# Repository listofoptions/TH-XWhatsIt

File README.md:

# TH-XWhatsIt

through hole implementation of the capsense controllers by XWhatsIt
(Tom Wong-Cornell). original liscencure holds, as well as CERN OSH
(compatible license).

original implementation of Tom Wong-Cornell's controller documented here

http://downloads.cornall.co/ibm-capsense-usb-web/ibm-capsense-usb.html

component documentation is supplied, working theory of operation is under
the previous link.

Please read the following files:

* [BOM.md](BOM.md) for Bill Of Materials.
* [ERRATA.md](ERRATA.md) for changes that must be made to older revision boards.
* [CHANGES.txt](CHANGES.txt) for all the detailed changes to this project over time.
* [PCB_ORDERING_INSTRUCTIONS.md](PCB_ORDERING_INSTRUCTIONS.md) for some notes on how to order PCBs.

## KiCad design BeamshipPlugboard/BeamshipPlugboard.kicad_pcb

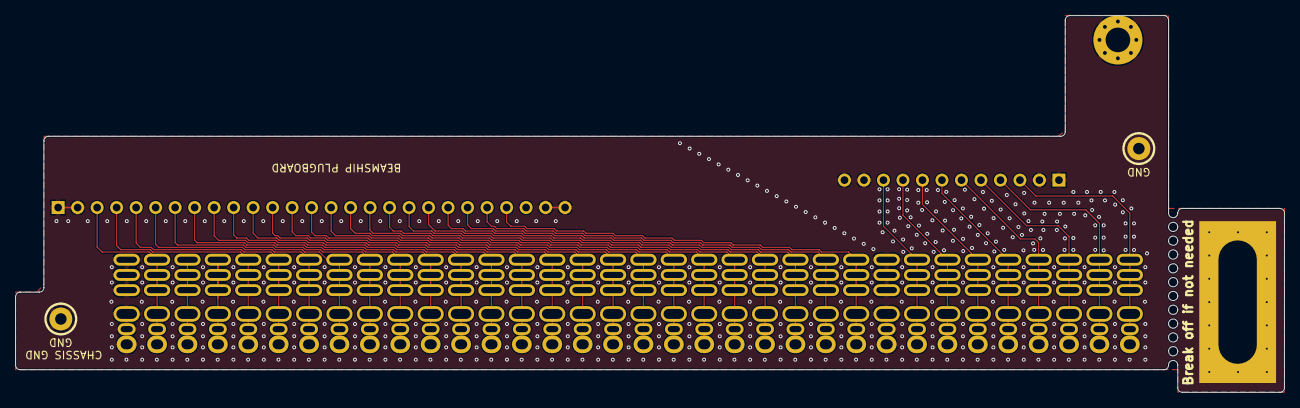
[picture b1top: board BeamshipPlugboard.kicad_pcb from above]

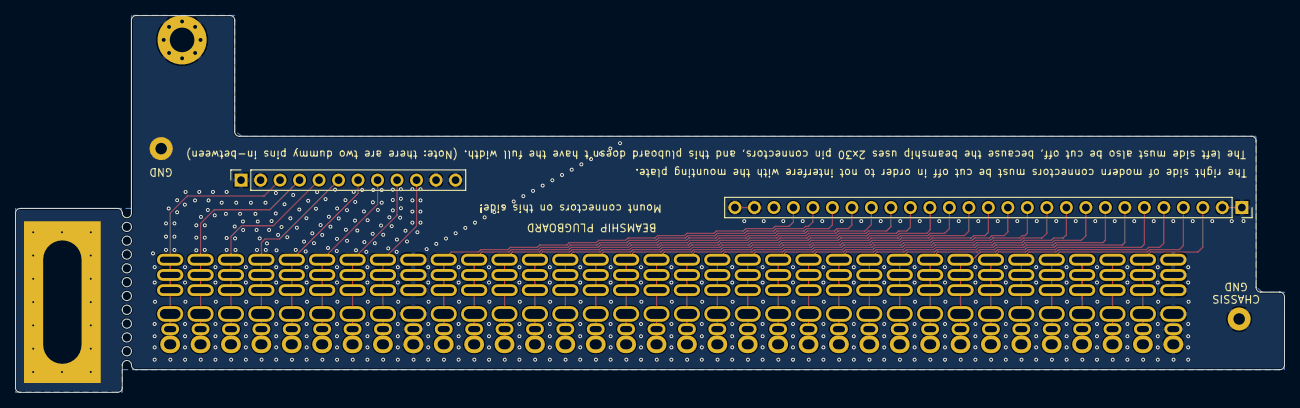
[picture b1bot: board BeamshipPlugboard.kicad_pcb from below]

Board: 2 copper layers, 165.3 x 49.1 mm, 7 parts (2 on the bottom side), 31 nets.

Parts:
H1: Grounded hole for M3 standoff; MountingHole_3.2mm_M3_Pad_Via
H2: BEAMSHIP MOUNTING HOLE; beamship_mounting_hole
H3, H4: GROUND STRAP; ChassisGnd
J1: BEAMSPRING PLUGBOARD COLUMNS; PinSocket_1x27_P2.54mm_Vertical
J2: BEAMSPRING PLUGBOARD ROWS; PinSocket_1x12_P2.54mm_Vertical
J7: Conn_01x34; beamship_new_2

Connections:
/BSCOL1: J1.3, J7.2
/BSCOL2: J1.4, J7.5
/BSCOL3: J1.5, J7.6
/BSCOL4: J1.6, J7.7
/BSCOL5: J1.7, J7.8
/BSCOL6: J1.8, J7.9
/BSCOL7: J1.9, J7.10
/BSCOL8: J1.10, J7.11
/BSCOL9: J1.11, J7.12
/BSCOL10: J1.12, J7.13
/BSCOL11: J1.13, J7.14
/BSCOL12: J1.14, J7.15
/BSCOL13: J1.15, J7.16
/BSCOL14: J1.16, J7.17
/BSCOL15: J1.17, J7.18
/BSCOL16: J1.18, J7.19
/BSCOL17: J1.19, J7.20
/BSCOL18: J1.20, J7.21
/BSCOL19: J1.21, J7.22
/BSCOL20: J1.22, J7.23
/BSCOL21: J1.23, J7.24
/BSCOL22: J1.24, J7.25
/BSGROUND: H1.1, H2.1, H3.1, H4.1, J1.1, J1.2, J1.26, J1.27, J2.1, J2.2, J2.11, J2.12, J7.1, J7.26
/BSSENSE1: J2.10, J7.27
/BSSENSE2: J2.9, J7.28
/BSSENSE3: J2.8, J7.29
/BSSENSE4: J2.7, J7.30
/BSSENSE5: J2.6, J7.31
/BSSENSE6: J2.5, J7.32
/BSSENSE7: J2.4, J7.33
/BSSENSE8: J2.3, J7.34

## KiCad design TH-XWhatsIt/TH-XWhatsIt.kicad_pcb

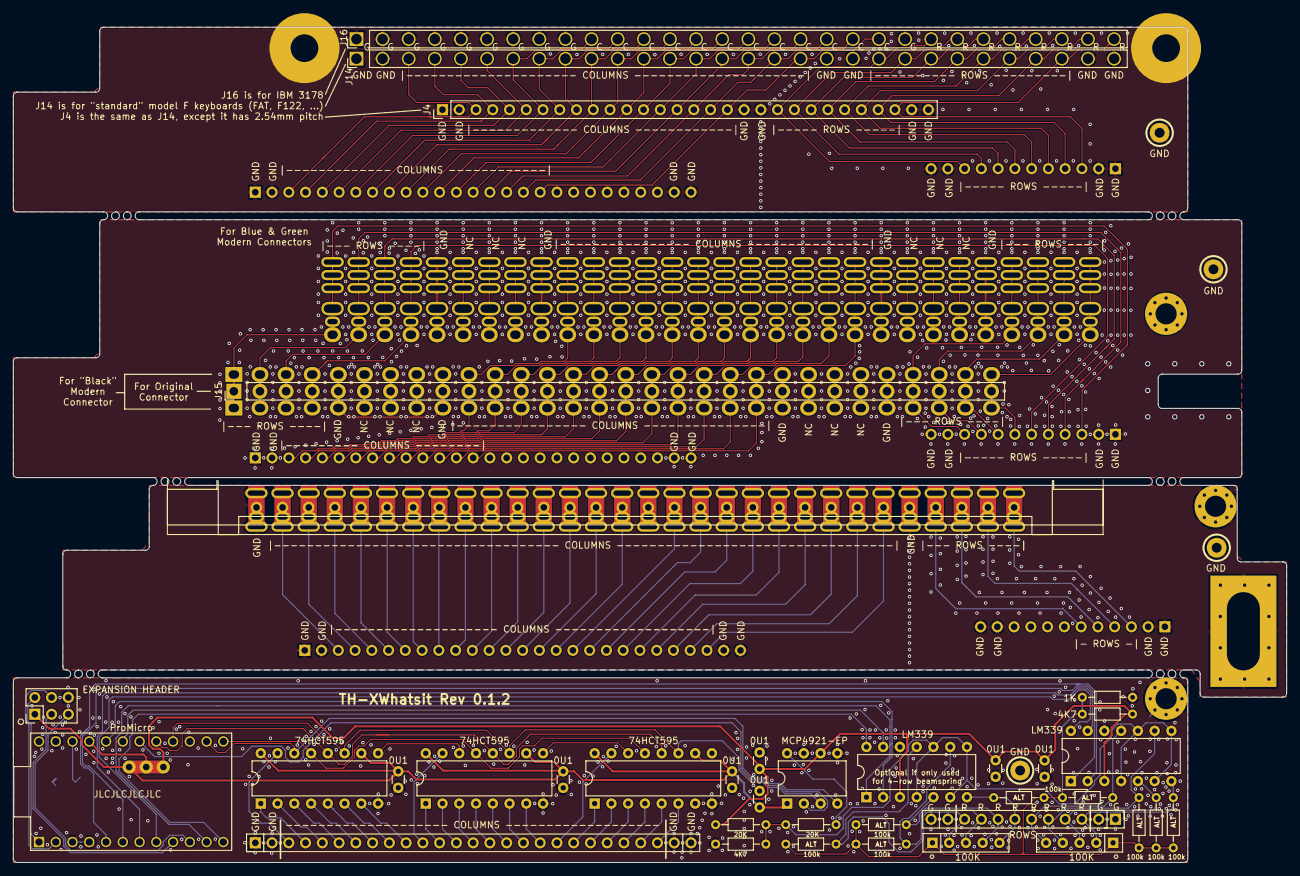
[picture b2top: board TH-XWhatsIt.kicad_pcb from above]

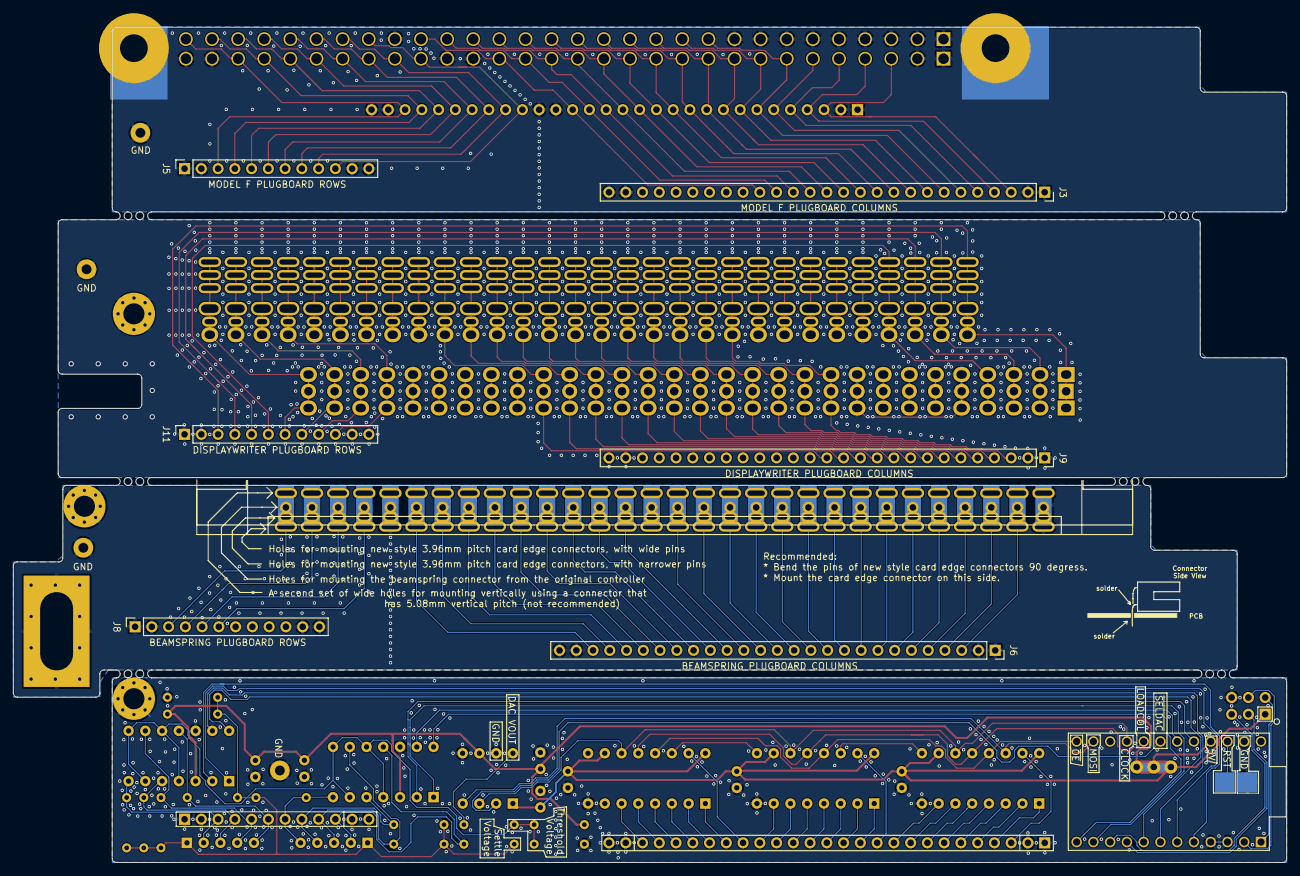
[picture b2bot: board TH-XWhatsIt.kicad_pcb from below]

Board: 2 copper layers, 193.0 x 126.6 mm, 56 parts (9 on the bottom side), 132 nets.

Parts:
C3, C4, C5, C7, C8, C9, C10: 0U1; C_Disc_D3.0mm_W1.6mm_P2.50mm
H1, H3, H4: Grounded hole for M3 standoff; MountingHole_3.2mm_M3_Pad_Via
H5: Beamspring Mounting Hole; BeamSpringGroundingMountingHoleForTHOnly
H6, H7, H8, H9: Solderable ground strap; ChassisGnd
H10: Left Mountinghole; ModelF_new_mounting_hole_left
H11: Right Mountinghole; ModelF_new_mounting_hole_right
J1: COLUMNS; PinHeader_1x27_P2.54mm_Vertical
J2: ROWS; PinHeader_1x12_P2.54mm_Vertical
J3: MODEL F PLUGBOARD COLUMNS; PinSocket_1x27_P2.54mm_Vertical
J4: MODEL F PLUGBOARD CONNECTOR; PinHeader_1x30_P2.54mm_Vertical
J5: MODEL F PLUGBOARD ROWS; PinSocket_1x12_P2.54mm_Vertical
J6: BEAMSPRING PLUGBOARD COLUMNS; PinSocket_1x27_P2.54mm_Vertical
J7: BEAMSPRING PLUGBOARD CONNECTOR; beamspring_connector_footprint
J8: BEAMSPRING PLUGBOARD ROWS; PinSocket_1x12_P2.54mm_Vertical
J9: DISPLAYWRITER PLUGBOARD COLUMNS; PinSocket_1x27_P2.54mm_Vertical
J10: Conn_01x30; displaywriter-connector_v3
J11: DISPLAYWRITER PLUGBOARD ROWS; PinSocket_1x12_P2.54mm_Vertical
J12: EXPANSION HEADER; PinHeader_2x03_P2.54mm_Vertical
J13: Conn_01x02; PadsToShort
J14, J16: MODEL F PLUGBOARD CONNECTOR; Model_F_3.96mm_pitch_footprint
J15: Conn_01x30; Displaywriter_with_mountinghole_footprint
NT2: Net-Tie_3; NetTie-3_THT_Pad1.0mm_mod_thicker
R1, R5: 4K7; R_Axial_DIN0204_L3.6mm_D1.6mm_P7.62mm_Horizontal
R2: 1K; R_Axial_DIN0204_L3.6mm_D1.6mm_P7.62mm_Horizontal
R3, R4: 20K; R_Axial_DIN0204_L3.6mm_D1.6mm_P7.62mm_Horizontal
R6, R7, R8, R9, R10, R11, R12, R13: 100k; R_Axial_DIN0204_L3.6mm_D1.6mm_P7.62mm_Horizontal
RN1, RN3: 100K; R_Array_SIP5
U1, U6: LM339; DIP-14_W7.62mm
U2: MCP4921-EP; DIP-8_W7.62mm
U3, U5, U8: 74HCT595; DIP-16_W7.62mm
U7: ProMicro

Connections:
+5VA: C4.2, C9.2, C10.2, NT2.3, R1.1, R3.2, U1.3, U2.6, U6.3
+5VD: C3.2, C5.2, C7.2, C8.2, J12.1, NT2.1, U2.1, U3.10, U3.16, U5.10, U5.16, U8.10, U8.16
/beamspring plugboard/BSCOL1: J6.3, J7.2
/beamspring plugboard/BSCOL2: J6.4, J7.3
/beamspring plugboard/BSCOL3: J6.5, J7.4
/beamspring plugboard/BSCOL4: J6.6, J7.5
/beamspring plugboard/BSCOL5: J6.7, J7.6
/beamspring plugboard/BSCOL6: J6.8, J7.7
/beamspring plugboard/BSCOL7: J6.9, J7.8
/beamspring plugboard/BSCOL8: J6.10, J7.9
/beamspring plugboard/BSCOL9: J6.11, J7.10
/beamspring plugboard/BSCOL10: J6.12, J7.11
/beamspring plugboard/BSCOL11: J6.13, J7.12
/beamspring plugboard/BSCOL12: J6.14, J7.13
/beamspring plugboard/BSCOL13: J6.15, J7.14
/beamspring plugboard/BSCOL14: J6.16, J7.15
/beamspring plugboard/BSCOL15: J6.17, J7.17
/beamspring plugboard/BSCOL16: J6.18, J7.18
/beamspring plugboard/BSCOL17: J6.19, J7.19
/beamspring plugboard/BSCOL18: J6.20, J7.20
/beamspring plugboard/BSCOL19: J6.21, J7.21
/beamspring plugboard/BSCOL20: J6.22, J7.22
/beamspring plugboard/BSCOL21: J6.23, J7.23
/beamspring plugboard/BSCOL22: J6.24, J7.24
/beamspring plugboard/BSCOL23: J6.25, J7.25
/beamspring plugboard/BSGROUND: H3.1, H5.1, H8.1, J6.1, J6.2, J6.26, J6.27, J7.1, J7.26, J8.1, J8.2, J8.11, J8.12
/beamspring plugboard/BSSENSE1: J7.27, J8.6
/beamspring plugboard/BSSENSE2: J7.28, J8.5
/beamspring plugboard/BSSENSE3: J7.29, J8.4
/beamspring plugboard/BSSENSE4: J7.30, J8.3
/displaywriter plugboard/DWCOL1: J9.3, J10.10, J15.10
/displaywriter plugboard/DWCOL2: J9.4, J10.11, J15.11
/displaywriter plugboard/DWCOL3: J9.5, J10.12, J15.12
/displaywriter plugboard/DWCOL4: J9.6, J10.13, J15.13
/displaywriter plugboard/DWCOL5: J9.7, J10.14, J15.14
/displaywriter plugboard/DWCOL6: J9.8, J10.15, J15.15
/displaywriter plugboard/DWCOL7: J9.9, J10.16, J15.16
/displaywriter plugboard/DWCOL8: J9.10, J10.17, J15.17
/displaywriter plugboard/DWCOL9: J9.11, J10.18, J15.18
/displaywriter plugboard/DWCOL10: J9.12, J10.19, J15.19
/displaywriter plugboard/DWCOL11: J9.13, J10.20, J15.20
/displaywriter plugboard/DWCOL12: J9.14, J10.21, J15.21
/displaywriter plugboard/DWGROUND: H4.1, H9.1, J9.1, J9.2, J9.26, J9.27, J10.5, J10.9, J10.22, J10.26, J11.1, J11.2, J11.11, J11.12, J15.5, J15.9, J15.22, J15.26
/displaywriter plugboard/DWSENSE1: J10.1, J11.3, J15.1
/displaywriter plugboard/DWSENSE2: J10.2, J11.4, J15.2
/displaywriter plugboard/DWSENSE3: J10.3, J11.5, J15.3
/displaywriter plugboard/DWSENSE4: J10.4, J11.6, J15.4
/displaywriter plugboard/DWSENSE5: J10.27, J11.10, J15.27
/displaywriter plugboard/DWSENSE6: J10.28, J11.9, J15.28
/displaywriter plugboard/DWSENSE7: J10.29, J11.8, J15.29
/displaywriter plugboard/DWSENSE8: J10.30, J11.7, J15.30
/model f plugboard/MFCOL1: J3.3, J4.3, J14.3
/model f plugboard/MFCOL2: J3.4, J4.4, J14.4
/model f plugboard/MFCOL3: J3.5, J4.5, J14.5
/model f plugboard/MFCOL4: J3.6, J4.6, J14.6
/model f plugboard/MFCOL5: J3.7, J4.7, J14.7, J16.10
/model f plugboard/MFCOL6: J3.8, J4.8, J14.8, J16.11
/model f plugboard/MFCOL7: J3.9, J4.9, J14.9, J16.12
/model f plugboard/MFCOL8: J3.10, J4.10, J14.10, J16.13
/model f plugboard/MFCOL9: J3.11, J4.11, J14.11, J16.14
/model f plugboard/MFCOL10: J3.12, J4.12, J14.12, J16.15
/model f plugboard/MFCOL11: J3.13, J4.13, J14.13, J16.16
/model f plugboard/MFCOL12: J3.14, J4.14, J14.14, J16.17
/model f plugboard/MFCOL13: J3.15, J4.15, J14.15, J16.18
/model f plugboard/MFCOL14: J3.16, J4.16, J14.16, J16.19
/model f plugboard/MFCOL15: J3.17, J4.17, J14.17, J16.20
/model f plugboard/MFCOL16: J3.18, J4.18, J14.18, J16.21
/model f plugboard/MFGROUND: H7.1, H10.1, H11.1, J3.1, J3.2, J3.26, J3.27, J4.1, J4.2, J4.19, J4.20, J4.29, J4.30, J5.1, J5.2, J5.11, J5.12, J14.1, J14.2, J14.19, J14.20, J14.29, J14.30, J16.1, J16.2, J16.3, J16.4, J16.5, J16.6, J16.7, J16.8, J16.9, J16.22
/model f plugboard/MFSENSE1: J4.21, J5.10, J14.21, J16.23
/model f plugboard/MFSENSE2: J4.22, J5.9, J14.22, J16.24
/model f plugboard/MFSENSE3: J4.23, J5.8, J14.23, J16.25
/model f plugboard/MFSENSE4: J4.24, J5.7, J14.24, J16.26
/model f plugboard/MFSENSE5: J4.25, J5.6, J14.25, J16.27
/model f plugboard/MFSENSE6: J4.26, J5.5, J14.26, J16.28
/model f plugboard/MFSENSE7: J4.27, J5.4, J14.27, J16.29
/model f plugboard/MFSENSE8: J4.28, J5.3, J14.28, J16.30
BIAS: R1.2, R2.1, R6.1, R7.1, R8.1, R9.1, R10.1, R11.1, R12.1, R13.1, RN1.1, RN3.1
CLOCK: U2.3, U3.11, U5.11, U7.16, U8.11
COL1: J1.3, U3.15
COL2: J1.4, U3.1
COL3: J1.5, U3.2
COL4: J1.6, U3.3
COL5: J1.7, U3.4
COL6: J1.8, U3.5
COL7: J1.9, U3.6
COL8: J1.10, U3.7
COL9: J1.11, U5.15
COL10: J1.12, U5.1
COL11: J1.13, U5.2
COL12: J1.14, U5.3
COL13: J1.15, U5.4
COL14: J1.16, U5.5
COL15: J1.17, U5.6
COL16: J1.18, U5.7
COL17: J1.19, U8.15
COL18: J1.20, U8.1
COL19: J1.21, U8.2
COL20: J1.22, U8.3
COL21: J1.23, U8.4
COL22: J1.24, U8.5
COL23: J1.25, U8.6
GND: C3.1, C4.1, C5.1, C7.1, C8.1, C9.1, C10.1, H1.1, H6.1, J1.1, J1.2, J1.26, J1.27, J2.1, J2.2, J2.11, J2.12, J12.6, J13.1, R2.2, R5.1, U1.12, U2.5, U2.7, U3.8, U5.8, U6.12, U7.3, U7.4, U7.23, U8.8
HEADER1: J12.3, U7.9
HEADER2: J12.5, U7.10
HEADER3: J12.2, U7.1
HEADER4: J12.4, U7.2
LOADCOL: U3.12, U5.12, U7.17, U8.12
MOSI: U2.4, U3.14, U7.14
unnamed: R4.2, U2.8
RESET: J13.2, U7.22
ROW1: U1.1, U7.6
ROW2: U1.2, U7.5
ROW3: U1.14, U7.8
ROW4: U1.13, U7.7
ROW5: U6.1, U7.11
ROW6: U6.14, U7.12
ROW7: U6.2, U7.20
ROW8: U6.13, U7.19
SENSE1: J2.3, R6.2, RN1.2, U1.7
SENSE2: J2.4, R12.2, RN1.3, U1.5
SENSE3: J2.5, R8.2, RN1.4, U1.9
SENSE4: J2.6, R7.2, RN1.5, U1.11
SENSE5: J2.7, R9.2, RN3.5, U6.7
SENSE6: J2.9, R11.2, RN3.3, U6.9
SENSE7: J2.8, R13.2, RN3.4, U6.5
SENSE8: J2.10, R10.2, RN3.2, U6.11
SERIALOUT1: U3.9, U5.14
SERIALOUT2: U5.9, U8.14
SETPOINT: R3.1, R4.1, R5.2, U1.4, U1.6, U1.8, U1.10, U6.4, U6.6, U6.8, U6.10
VCC: NT2.2, U7.21
~OE: U3.13, U5.13, U7.13, U8.13
~SELECTDAC: U2.2, U7.18

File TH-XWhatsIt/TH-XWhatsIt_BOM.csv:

"Id";"Designator";"Package";"Quantity";"Designation";"Supplier and ref";
1;"U7";"ProMicro";1;"ProMicro";;;
2;"J2";"PinHeader_1x12_P2.54mm_Vertical";1;"ROWS";;;
3;"J1";"PinHeader_1x27_P2.54mm_Vertical";1;"COLUMNS";;;
4;"J8";"PinSocket_1x12_P2.54mm_Vertical";1;"BEAMSPRING PLUGBOARD ROWS";;;
5;"J11";"PinSocket_1x12_P2.54mm_Vertical";1;"DISPLAYWRITER PLUGBOARD ROWS";;;
6;"J5";"PinSocket_1x12_P2.54mm_Vertical";1;"MODEL F PLUGBOARD ROWS";;;
7;"J9";"PinSocket_1x27_P2.54mm_Vertical";1;"DISPLAYWRITER PLUGBOARD COLUMNS";;;
8;"J3";"PinSocket_1x27_P2.54mm_Vertical";1;"MODEL F PLUGBOARD COLUMNS";;;
9;"J6";"PinSocket_1x27_P2.54mm_Vertical";1;"BEAMSPRING PLUGBOARD COLUMNS";;;
10;"J10";"DIP-60_155_ELL";1;"DISPLAYWRITER PLUGBOARD CONNECTOR";;;
11;"J4";"PinHeader_1x30_P2.54mm_Horizontal";1;"MODEL F PLUGBOARD CONNECTOR";;;
12;"J7";"3..6mm_cardedge";1;"BEAMSPRING PLUGBOARD CONNECTOR";;;
13;"U1,U6";"DIP-14_W7.62mm";2;"LM339";;;
14;"R6,R5,R1";"R_Axial_DIN0204_L3.6mm_D1.6mm_P1.90mm_Vertical";3;"4K7";;;
15;"R2,R7";"R_Axial_DIN0204_L3.6mm_D1.6mm_P1.90mm_Vertical";2;"1K";;;
16;"RN3,RN1";"R_Array_SIP5";2;"100K";;;
17;"J12";"PinHeader_2x03_P2.54mm_Vertical";1;"EXPANSION HEADER";;;
18;"RN2,RN4";"R_Array_SIP5";2;"10K";;;
19;"C3,C4,C5,C7,C8,C9,C10";"C_Disc_D3.0mm_W1.6mm_P2.50mm";7;"0U1";;;
20;"R3,R4";"R_Axial_DIN0204_L3.6mm_D1.6mm_P1.90mm_Vertical";2;"20K";;;
21;"U2";"DIP-8_W7.62mm";1;"MCP4921-EP";;;
22;"U8,U5,U3";"DIP-16_W7.62mm";3;"74HCT595";;;
23;"C2";"C_Disc_D3.0mm_W1.6mm_P2.50mm";1;"10U";;;
24;"H1,H2,H3,H4";"MountingHole_2.2mm_M2_Pad_Via";4;"GROUND STRAP";;;

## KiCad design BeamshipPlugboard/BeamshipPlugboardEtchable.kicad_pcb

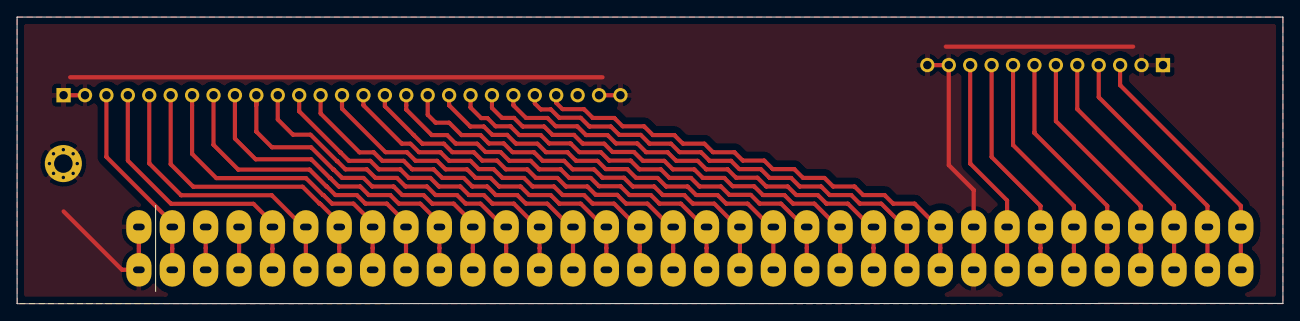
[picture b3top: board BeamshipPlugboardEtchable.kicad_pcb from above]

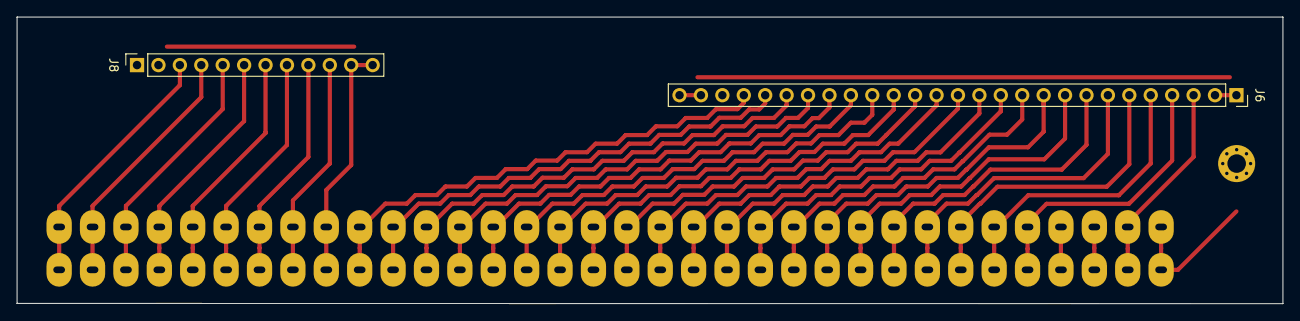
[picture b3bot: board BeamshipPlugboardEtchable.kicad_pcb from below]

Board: 2 copper layers, 150.1 x 34.0 mm, 4 parts (2 on the bottom side), 31 nets.

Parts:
H3: GROUND STRAP; MountingHole_2.2mm_M2_Pad_Via
J6: BEAMSPRING PLUGBOARD COLUMNS; PinSocket_1x27_P2.54mm_Vertical
J7: Conn_01x34; cardedge_beamship
J8: BEAMSPRING PLUGBOARD ROWS; PinSocket_1x12_P2.54mm_Vertical

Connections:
/beamspring plugboard/BSCOL1: J6.3, J7.2
/beamspring plugboard/BSCOL2: J6.4, J7.5
/beamspring plugboard/BSCOL3: J6.5, J7.6
/beamspring plugboard/BSCOL4: J6.6, J7.7
/beamspring plugboard/BSCOL5: J6.7, J7.8
/beamspring plugboard/BSCOL6: J6.8, J7.9
/beamspring plugboard/BSCOL7: J6.9, J7.10
/beamspring plugboard/BSCOL8: J6.10, J7.11
/beamspring plugboard/BSCOL9: J6.11, J7.12
/beamspring plugboard/BSCOL10: J6.12, J7.13
/beamspring plugboard/BSCOL11: J6.13, J7.14
/beamspring plugboard/BSCOL12: J6.14, J7.15
/beamspring plugboard/BSCOL13: J6.15, J7.16
/beamspring plugboard/BSCOL14: J6.16, J7.17
/beamspring plugboard/BSCOL15: J6.17, J7.18
/beamspring plugboard/BSCOL16: J6.18, J7.19
/beamspring plugboard/BSCOL17: J6.19, J7.20
/beamspring plugboard/BSCOL18: J6.20, J7.21
/beamspring plugboard/BSCOL19: J6.21, J7.22
/beamspring plugboard/BSCOL20: J6.22, J7.23
/beamspring plugboard/BSCOL21: J6.23, J7.24
/beamspring plugboard/BSCOL22: J6.24, J7.25
/beamspring plugboard/BSGROUND: H3.1, J6.1, J6.2, J6.26, J6.27, J7.1, J7.26, J8.1, J8.2, J8.11, J8.12
/beamspring plugboard/BSSENSE1: J7.27, J8.10
/beamspring plugboard/BSSENSE2: J7.28, J8.9
/beamspring plugboard/BSSENSE3: J7.29, J8.8
/beamspring plugboard/BSSENSE4: J7.30, J8.7
/beamspring plugboard/BSSENSE5: J7.31, J8.6
/beamspring plugboard/BSSENSE6: J7.32, J8.5
/beamspring plugboard/BSSENSE7: J7.33, J8.4
/beamspring plugboard/BSSENSE8: J7.34, J8.3

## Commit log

2020-02-04 version bump to 2.0 due to header position changes finished wiring up most of the plugboards, but displaywriter as per usual is the most annoying.....see changes file for more details (jan 3rd, 2020)
2020-02-04 finished wiring the dispalywriter plugboard, and added grounding straps to plugboards
2020-05-25 Adding BOM and GERBER files for PCB production as 10t8or agreed with kmnov
2020-07-07 rumors of my demise are greatly exaggerated, updates; more incoming now powered with new pc! thanks for being patient, please inform of futher changes!
2020-08-14 initial update to switch to smd, so now th prefix is a misnomer
2020-08-15 fix typo in readme
2020-08-15 Removed backup files, and made gitignore not show them
2020-08-15 Schematics: shift register OE pins connected to GND, and unused ProMicro pin connected to gnd
2020-08-15 pcb: pushed update from schematic: (OE grounded)
2020-08-15 Remove .tmp files and add them to .gitignore
2020-08-15 removed autosave file, and added to gitignore
2020-08-15 Removed BOM, it was only correct for real TH controller
2020-08-15 symbol libraries: edit to use relative paths
2020-08-15 Schematic: added note about the purpose of the grounded promicro pins
2020-08-15 make footprint library references relative
2020-08-15 get rid of weird rescue library, and make reference to pro micro library relative
2020-08-15 Schematics: removed pins that looked like accidentally left over stuff
2020-08-15 Pro micro schematic symbol: changed SCL/SDA pin to show gpio port. The SCL/SDA marking was wrong anyway.
2020-08-15 pcb: made solenoid header footprint vertical, removed right side of controller PCB
2020-08-15 Reordered row to promicro pin connections to make sure that beamsprings only use two different ports
2020-08-15 pcb: move plugboards to the left, to demonstrate misalignment
2020-08-15 pcb: fix castellation alignment issues
2020-08-15 pcb: added cutout to displaywriter
2020-08-15 Added cutout to the beamspring plugboard
2020-08-15 changed resistor network footprint sizes to what's available from jlcpcb
2020-08-15 Added pads for easily shorting reset with a screwdriver
2020-08-15 pcb: removed some useless vias
2020-08-15 Fix courtyard on beamspring and displaywriter connector
2020-08-15 Added my new footprint for beamspring
2020-08-15 use improved footprint, and improved pin ordering for beamspring
2020-08-15 Using new footprint for displaywriter too
2020-08-15 Tweaks to displaywriter plugboard. Cutout rounded. More via stiching added
2020-08-16 Added beamspring mounting hole tab
2020-08-16 Moved all boards to the right to fit page
2020-08-22 Removed outdated gerber files
2020-08-22 Removed backup files, added gitignore
2020-08-22 Make sure libraries are found using relative paths
2020-08-22 Get rid of the rescue library
2020-08-22 Removed netlist
2020-08-22 Removed BOM. I can't seem to regenerate this format and keep it up to date, so removing it, since it's out-of-date
2020-08-22 Removed pull-ups from LM339 outputs. These will be provided in the atmega from now on.
2020-08-22 Fixed missing connection to ground strap
2020-08-22 Remove extra biasing resistors. Better for >4row keyboards.
2020-08-22 Made DAC output resistors horizontal
2020-08-22 Add option to use individual resistors to pull towards bias
2020-08-22 Renamed schematic title form THT-Xwhatsit to TH xwhatsit, bumped revision to 0.0.3, added revision to silkscreen, added changelog
2020-08-23 Added pads to short reset on bottom
2020-08-23 Use net tie to enforce star ground on the controller
2020-08-23 thicken up ground traces
2020-08-23 updated CHANGES.txt
2020-08-23 repositioned chips and resistors to make space for beamspring connector
2020-08-23 I'm just after realizing that this PCB was using the style where the component values are on silkscreen but not the RefDes. Making my changes match this style.
2020-08-23 Made net ties thicker
2020-08-23 Moved top-most resistors tiny bit to the right to potentially accomodate some beamspring connector configurations
2020-08-23 Added courtyard (measured by me) to pro micro footprint. Removed courtyard from net tie to avoid drc issues. Tweaked net tie clearence type to solid (will help when we add copper fill)
2020-08-23 beamspring plugboard: use new footprint, and add documentation about how to use it
2020-08-23 Added big oval mounting hole, Y position not yet final
2020-08-23 Small bugfix to the PadsToShort footprint, remove paste layer.
2020-08-23 Added beamspring mounting hole
2020-08-23 model F plugboard: added 3.96 mm connector too
2020-08-23 Clarified which type of connector is supported for vertical mounting
2020-08-23 displaywriter plugboard: Make sure we don't interfere with mounting plate. Add support for different vertical pin pitch connectors. Add support for original connector with mounting slot. Position of 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
2020-08-23 Beamship plugboard: added
2020-08-23 Added etchable variant of BeamshipPlugboard
2020-08-23 Changelog updated
2020-08-23 Beamship plugboard: fix orientation of text
2020-08-23 Added some notes to beamspring plugboard
2020-11-01 Various changes to revision 0.1.1
    General:
    Made mounting hole bigger (M3). And moved it a little bit so it doesn't interfere with some components.
    Star ground turned into single ground.
    Ground fills added everywhere.
    Many stitching vias added everywhere.
    Added JLCJLCJLCJLC magic string under pro micro. When ordering from JLCPCB, you can select for Order Number: "Specify Location"
2020-11-01 beamship: hid away leaking silkscreen
2020-11-01 Beamship: fix which side of the mounting hole has no solder mask
2020-11-07 fix up revision in title block on pcb file. (silkskreen already had the correct revision)
2020-11-07 Added BOM, ERRATA, and PCB_ORDERING_INSTRUCTIONS in markdown format
2020-11-07 fix some typos
2020-11-15 BOM updated:
    changed TME examples from carbon film resistors to metal film resistors
    recommendation that 100k resistors/resistor networks should be high precision.
    added LCSC examples
    added Aliexpress M3 standoff/screw/nut/washer/... kit
2020-11-15 BOM: updates(2)
    - reformatted some links
    - added Digi-Key bom items
    - added Mouser bom items
    - added link to OctoPart bom
2020-11-15 BOM: added tme bom csv and guide how to upload
2020-11-15 make tme_bom.csv a link
2020-12-13 Added locklights header, bumped revision
2020-12-13 Updated gerbers
2020-12-13 Made left side of all plugboards 1.5mm shorter (the cutout for the solenoid header is 1.5mm bigger)
    this makes some connectors fit more comfortably
2020-12-13 Updated BOM, changelog, and fixes CHANGES.txt to include accurate date for latest revision
2021-01-26 Beamship Plugboard: added extra grounding hole.
2021-05-03 Updated pro micro schematic symbol, with corrected pin names, and more verbose. No design change.
2021-05-03 fixed changes.txt to reference correct revision
2021-05-03 Added schematics for various revisions. (Using the corrected pro micro symbol), and updated errata.
2021-09-25 Add render, and include render in readme, so it shows up in github.
2021-09-25 Move gerbers.zip into its own folder

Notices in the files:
BeamshipPlugboard/BeamshipPlugboard.kicad_pcb:
Licenced under CERN OHL Version 1.2
Copyright Rainy Day Plans.
This documentation describes Open Hardware and is licensed under the
CERN OHL v. 1.2.
